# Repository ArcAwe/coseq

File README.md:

<i>coseq</i>
============

Cadet Open Source Extensible Quadcopter (COSEQ) Design Documents and Code.

Written and compiled by G. Holland Gibson - 2014
Originally as part of his Honors Project @ The United States Military Academy. 

Open Source
===========

This is a primarily open-source design (and work in progress) to accomplish 3 extensible and adaptable components that operate 
independently of each other in order to provide a stable airborne platform in a quadcopter form.

Written under the MIT license except where otherwise noted (using other peoples' open source code). See LICENSE for more info.

1] Hardware:
-----------
The Hardware is a very stable, and strong, yet lightweight construction

2] Controller: 
-------------
The controller uses Python running on a raspberry pi (battery powered) with a USB controller/gamepad.

3] Embedded Electronics: 
-----------------------
Parallax Propeller as host system.

Open Source / Freeware used:
============================
Google SketchUp
    http://www.sketchup.com/<br>
SimpleIDE
    http://learn.parallax.com/propeller-c-set-simpleide<br>
TextWrangler
    http://www.barebones.com/products/textwrangler/<br>
netfabb Basic
    http://www.netfabb.com/basic.php<br>

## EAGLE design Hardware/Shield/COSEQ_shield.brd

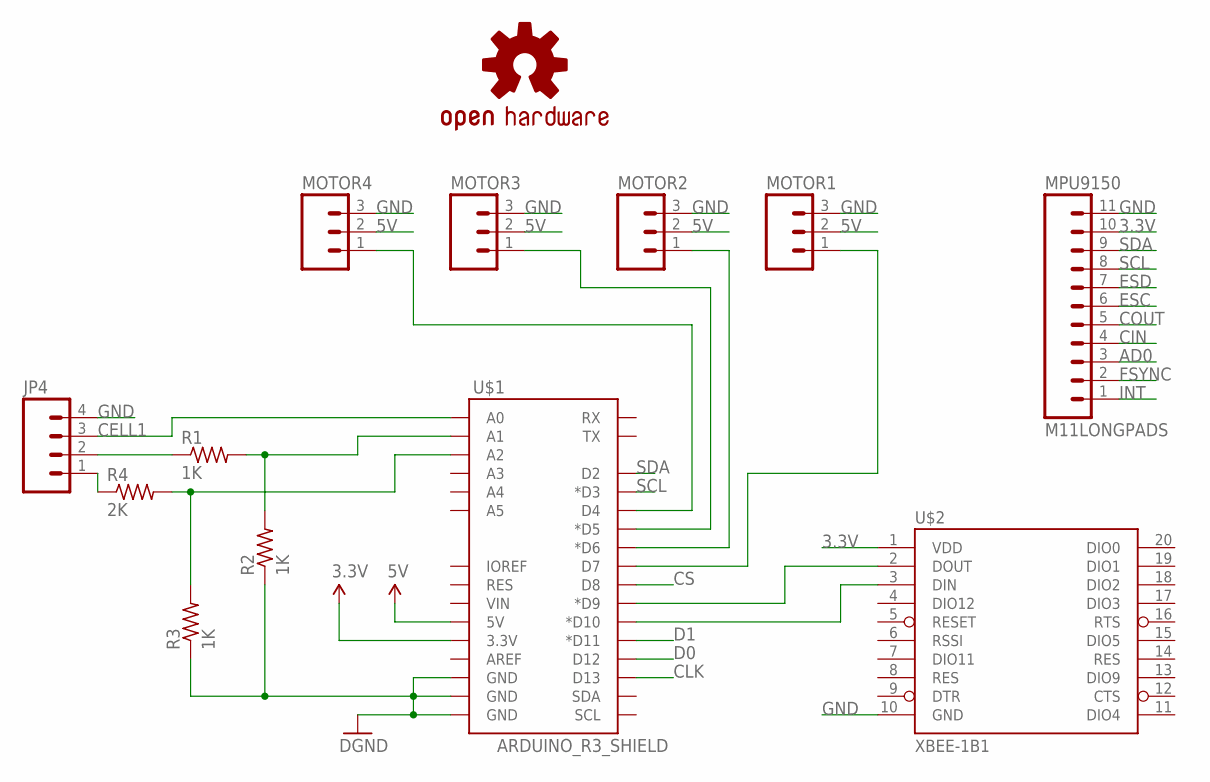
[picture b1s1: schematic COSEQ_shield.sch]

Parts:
JP4: M04LONGPADS; 1X04_LONGPADS
LOGO1: OSHW-LOGOL; OSHW-LOGO-L
MOTOR1, MOTOR2, MOTOR3, MOTOR4: M03LONGPADS; 1X03_LONGPADS
MPU9150: M11LONGPADS; 1X11_LONGPADS
R1, R2, R3: 1K; RESISTOR
R4: 2K; RESISTOR
U$1: ARDUINO_R3_SHIELD; UNO_R3_SHIELD
U$2: XBEE-1B1; XBEE-1

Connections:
3.3V: MPU9150.10, U$1.3.3V, U$2.1 (VDD)
5V: MOTOR1.2, MOTOR2.2, MOTOR3.2, MOTOR4.2, U$1.5V
AD0: MPU9150.3
CELL1: JP4.3, U$1.A0
CIN: MPU9150.4
CLK: U$1.D13
COUT: MPU9150.5
CS: U$1.D8
D0: U$1.D12
D1: U$1.D11 (*D11)
ESC: MPU9150.6
ESD: MPU9150.7
FSYNC: MPU9150.2
GND: JP4.4, MOTOR1.3, MOTOR2.3, MOTOR3.3, MOTOR4.3, MPU9150.11, R2.1, R3.1, U$1.GND@0 (GND), U$1.GND@1 (GND), U$1.GND@2 (GND), U$2.10 (GND)
INT: MPU9150.1
M1: MOTOR4.1, U$1.D4
M2: MOTOR3.1, U$1.D5 (*D5)
M3: MOTOR2.1, U$1.D6 (*D6)
M4: MOTOR1.1, U$1.D7
unnamed: JP4.2, R1.1
unnamed: U$1.D10 (*D10), U$2.3 (DIN)
unnamed: R1.2, R2.2, U$1.A1
unnamed: U$1.D9 (*D9), U$2.2 (DOUT)
unnamed: JP4.1, R4.1
unnamed: R3.2, R4.2, U$1.A2
SCL: MPU9150.8, U$1.D3 (*D3)
SDA: MPU9150.9, U$1.D2

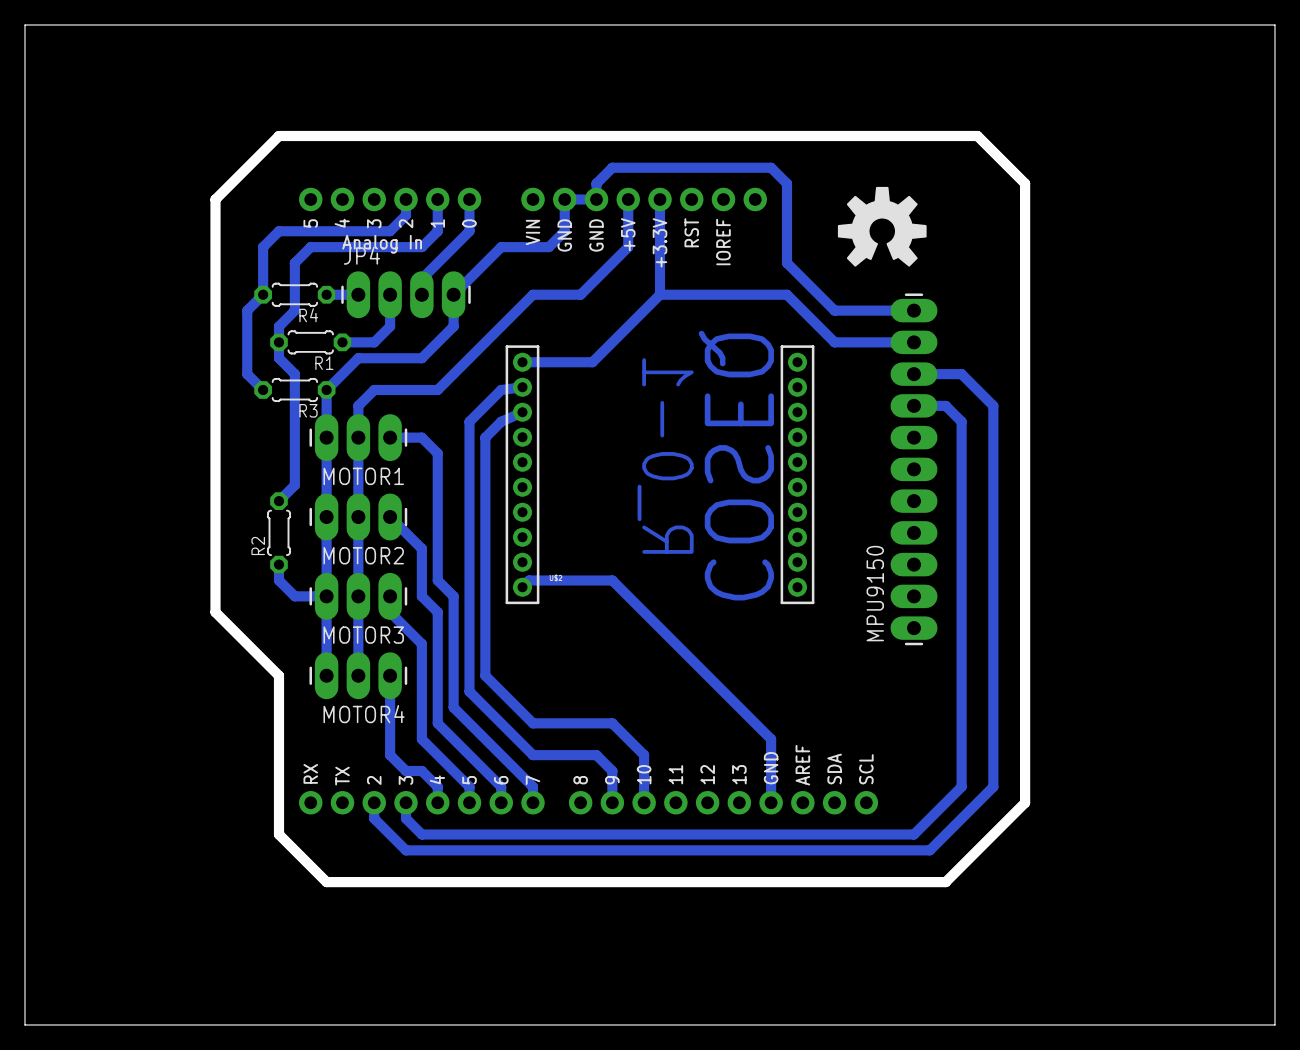
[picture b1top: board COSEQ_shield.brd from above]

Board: 2 copper layers, 100.0 x 80.0 mm, 13 parts (0 on the bottom side), 16 nets.

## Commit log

2014-04-30 Updated LICENSE to MIT license
2014-05-01 Adding pictures
2014-05-01 Added Hardware Directory
2014-05-01 Propeller Software
2014-05-01 Raspberry Pi Software
2014-05-01 Updated .gitignore and Presentation PDF
2014-05-01 Added cloc line counter
2014-05-01 More README updates
2014-05-01 Create gh-pages branch via GitHub
2014-05-01 Link
2014-05-02 Added .gitignore
2014-05-07 Added Eagle files for the ASC+ shield

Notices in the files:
parts and their libraries:
SparkFun-Boards: Licensing: CC v3.0 Share-Alike You are welcome to use this library for commercial purposes.
